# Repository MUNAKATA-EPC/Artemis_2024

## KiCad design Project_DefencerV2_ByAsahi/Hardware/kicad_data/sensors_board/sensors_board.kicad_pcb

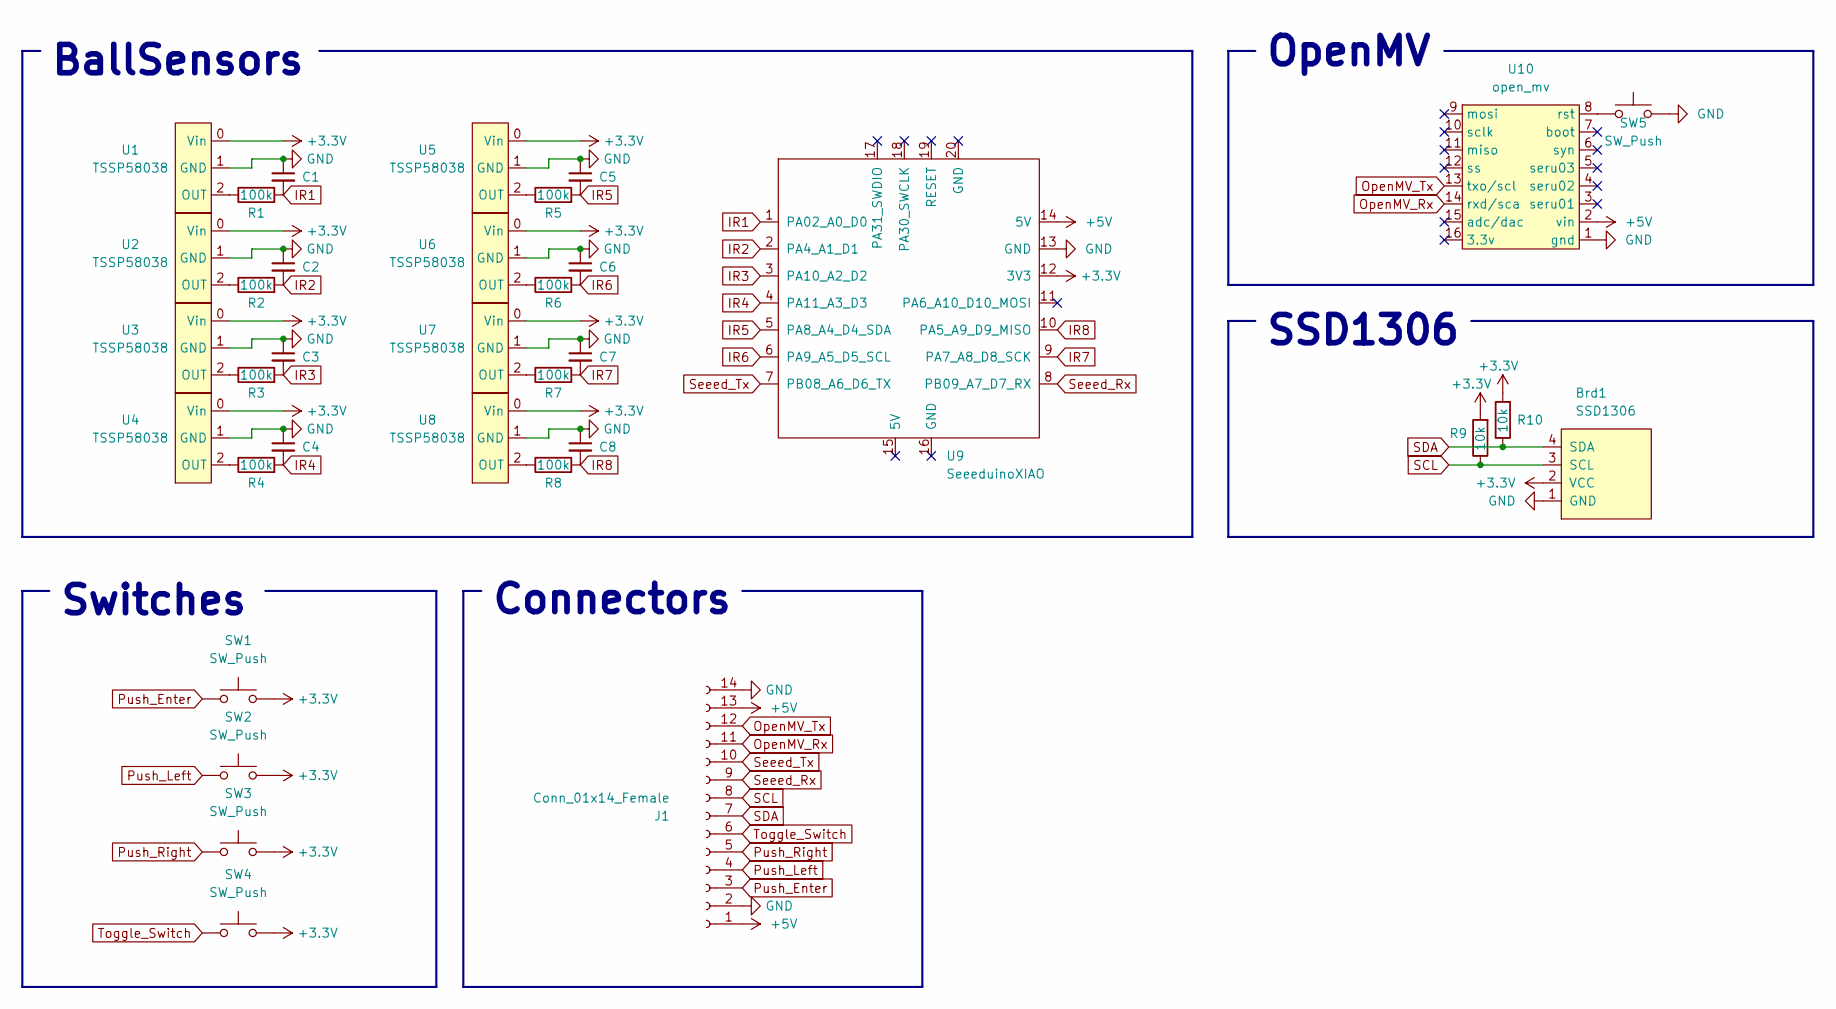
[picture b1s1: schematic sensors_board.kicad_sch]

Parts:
Brd1: SSD1306; 128x64OLED
C1, C2, C3, C4, C5, C6, C7, C8: C_Small; C_Disc_D3.0mm_W2.0mm_P2.50mm
J1: Conn_01x14_Female; IDC-Header_2x07_P2.54mm_Horizontal
R1, R2, R3, R4, R5, R6, R7, R8: 100k; R_Axial_DIN0204_L3.6mm_D1.6mm_P5.08mm_Horizontal
R9, R10: 10k; R_Axial_DIN0204_L3.6mm_D1.6mm_P5.08mm_Horizontal
SW1, SW2, SW3, SW5: SW_Push; SW_PUSH_6mm_H5mm
SW4: SW_Push; DS-850k
U1, U2, U3, U4, U5, U6, U7, U8: TSSP58038
U9: SeeeduinoXIAO; seeeduinoXIAO
U10: open_mv; OpenMV

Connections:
+3.3V: Brd1.2 (VCC), R9.2, R10.2, SW1.2, SW2.2, SW3.2, SW4.2, U1.0 (Vin), U2.0 (Vin), U3.0 (Vin), U4.0 (Vin), U5.0 (Vin), U6.0 (Vin), U7.0 (Vin), U8.0 (Vin), U9.12 (3V3)
+5V: J1.1, J1.13, U9.14 (5V), U10.2 (vin)
GND: Brd1.1 (GND), C1.1, C2.1, C3.1, C4.1, C5.1, C6.1, C7.1, C8.1, J1.2, J1.14, SW5.2, U1.1 (GND), U2.1 (GND), U3.1 (GND), U4.1 (GND), U5.1 (GND), U6.1 (GND), U7.1 (GND), U8.1 (GND), U9.13 (GND), U10.1 (gnd)
IR1: C1.2, R1.2, U9.1 (PA02_A0_D0)
IR2: C2.2, R2.2, U9.2 (PA4_A1_D1)
IR3: C3.2, R3.2, U9.3 (PA10_A2_D2)
IR4: C4.2, R4.2, U9.4 (PA11_A3_D3)
IR5: C5.2, R5.2, U9.5 (PA8_A4_D4_SDA)
IR6: C6.2, R6.2, U9.6 (PA9_A5_D5_SCL)
IR7: C7.2, R7.2, U9.9 (PA7_A8_D8_SCK)
IR8: C8.2, R8.2, U9.10 (PA5_A9_D9_MISO)
unnamed: R1.1, U1.2 (OUT)
unnamed: R2.1, U2.2 (OUT)
unnamed: R3.1, U3.2 (OUT)
unnamed: R4.1, U4.2 (OUT)
unnamed: R5.1, U5.2 (OUT)
unnamed: R6.1, U6.2 (OUT)
unnamed: R7.1, U7.2 (OUT)
unnamed: R8.1, U8.2 (OUT)
unnamed: SW5.1, U10.8 (rst)
OpenMV_Rx: J1.11, U10.14 (rxd/sca)
OpenMV_Tx: J1.12, U10.13 (txo/scl)
Push_Enter: J1.3, SW1.1
Push_Left: J1.4, SW2.1
Push_Right: J1.5, SW3.1
SCL: Brd1.3 (SCL), J1.8, R9.1
SDA: Brd1.4 (SDA), J1.7, R10.1
Seeed_Rx: J1.9, U9.8 (PB09_A7_D7_RX)
Seeed_Tx: J1.10, U9.7 (PB08_A6_D6_TX)
Toggle_Switch: J1.6, SW4.1

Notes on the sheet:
Connectors
SSD1306
BallSensors
Switches
OpenMV

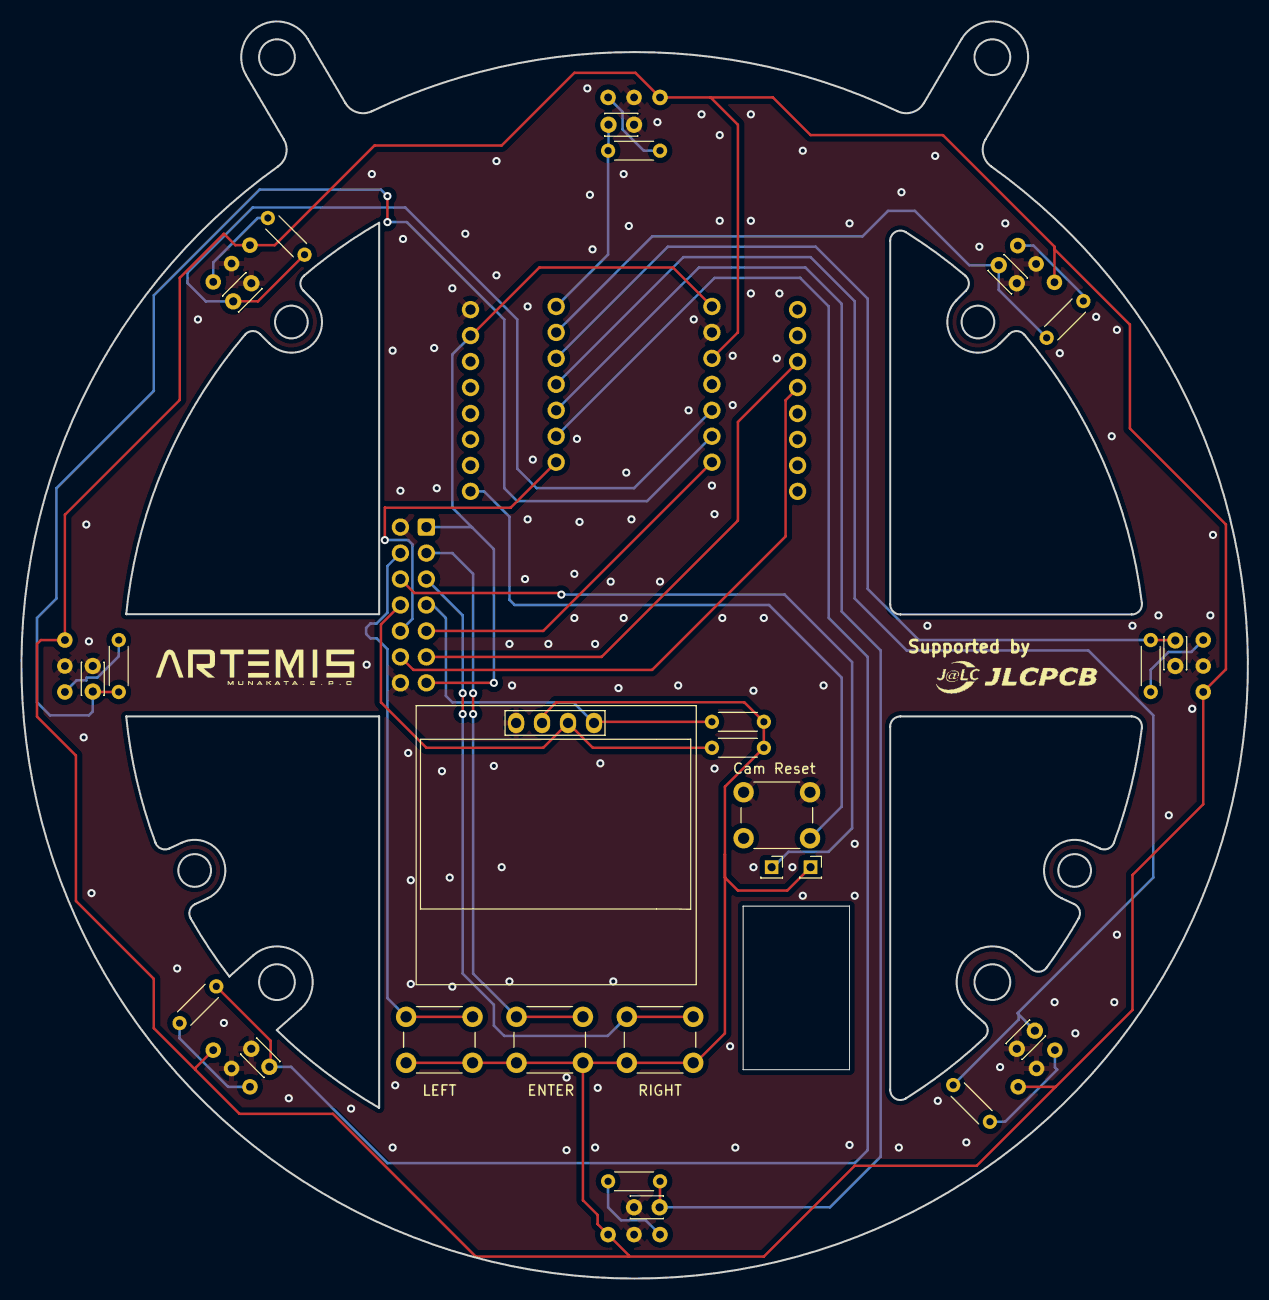
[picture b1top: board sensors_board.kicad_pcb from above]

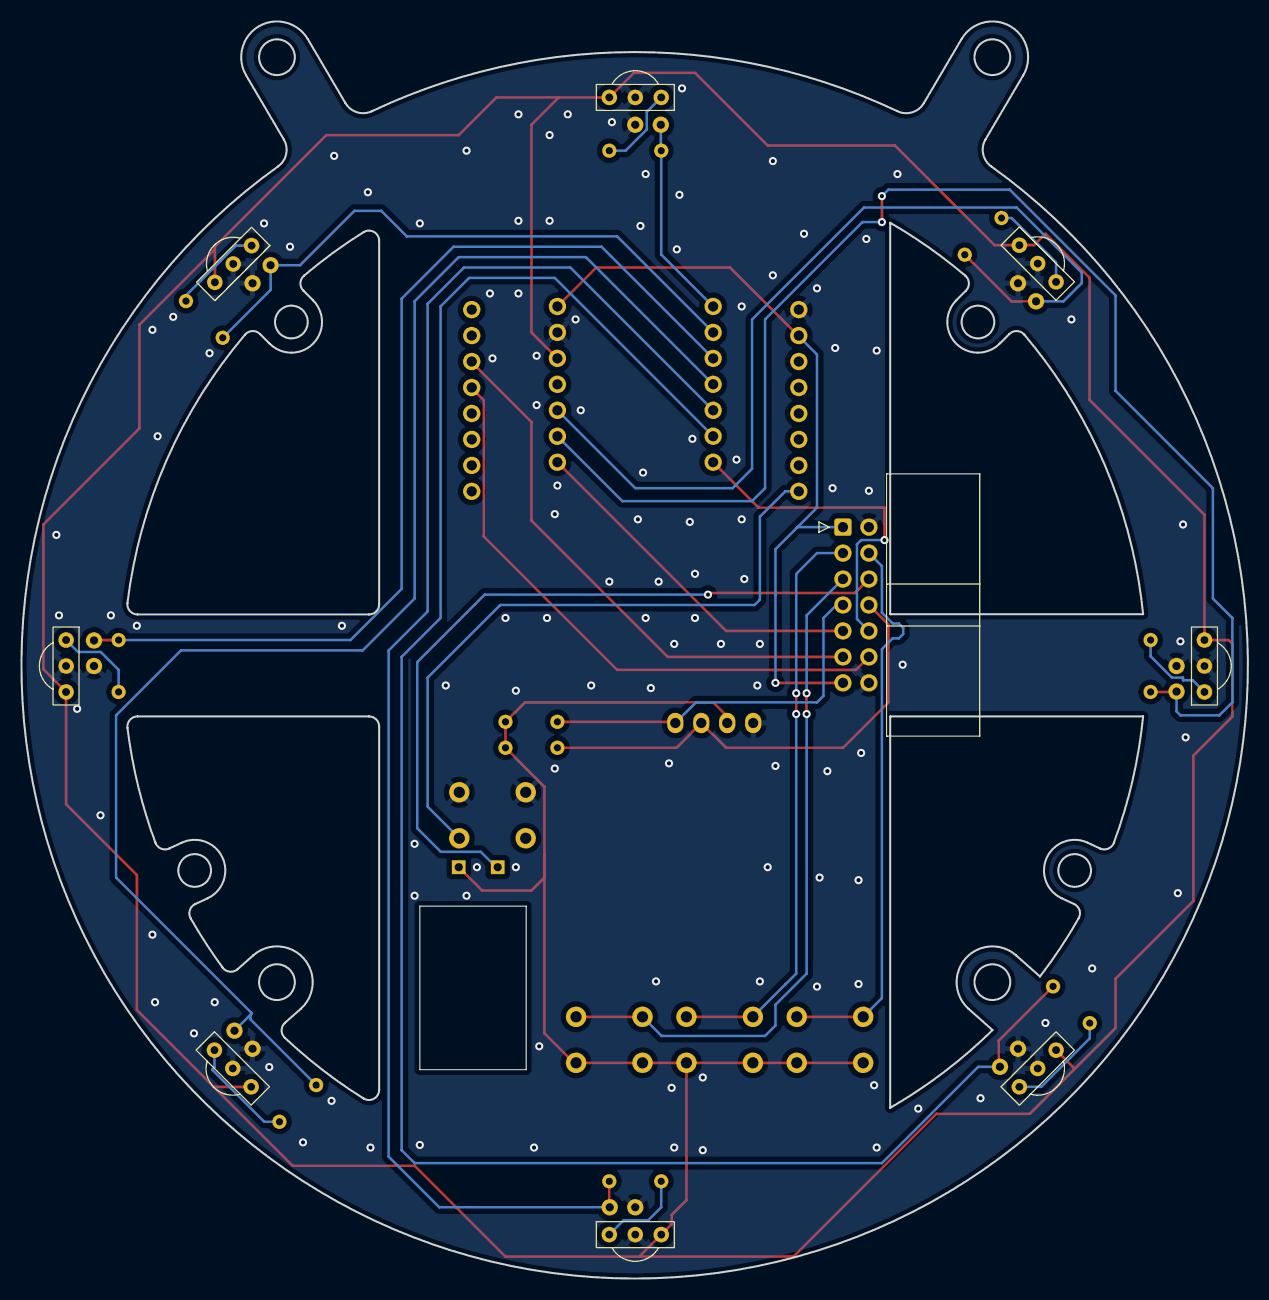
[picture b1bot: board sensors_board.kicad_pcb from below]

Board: 2 copper layers, 120.0 x 123.0 mm, 34 parts (10 on the bottom side), 29 nets.

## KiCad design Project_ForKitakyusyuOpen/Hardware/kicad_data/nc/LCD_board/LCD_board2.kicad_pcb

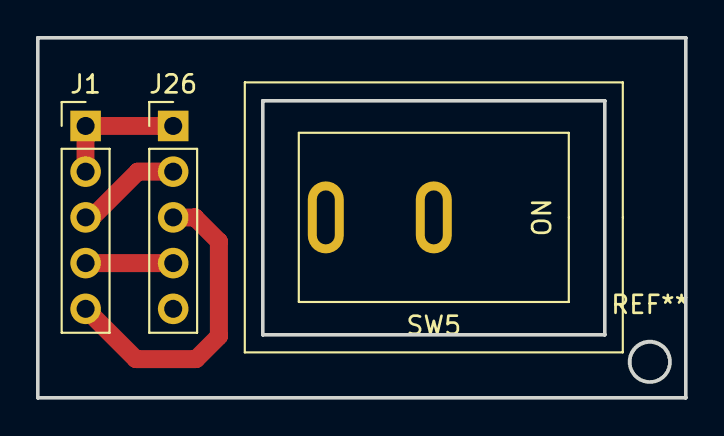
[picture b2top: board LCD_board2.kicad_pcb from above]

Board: 2 copper layers, 36.0 x 20.0 mm, 3 parts (0 on the bottom side), 5 nets.

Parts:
J1, J26: Conn_01x05_Socket; PinHeader_1x05_P2.54mm_Vertical
SW5: SW_DIP_x01; DS-850k

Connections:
+3V3: J1.1, J1.2, J26.1, SW5.1
D9: J26.5, SW5.2
GND: J1.5, J26.3
SCL0: J1.3, J26.2
SDA0: J1.4, J26.4

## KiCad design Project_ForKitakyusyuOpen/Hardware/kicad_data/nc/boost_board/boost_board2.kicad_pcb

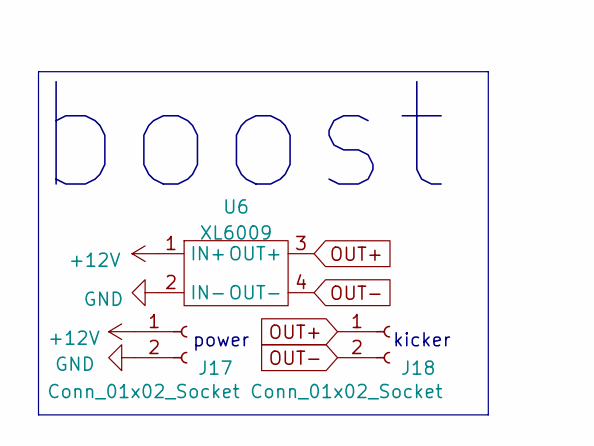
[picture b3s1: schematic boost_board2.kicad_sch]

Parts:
J17, J18: Conn_01x02_Socket; PinHeader_1x02_P2.54mm_Vertical
U6: XL6009

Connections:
+12V: J17.1, U6.1 (IN+)
GND: J17.2, U6.2 (IN-)
OUT+: J18.1, U6.3 (OUT+)
OUT-: J18.2, U6.4 (OUT-)

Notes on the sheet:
kicker
power
boost

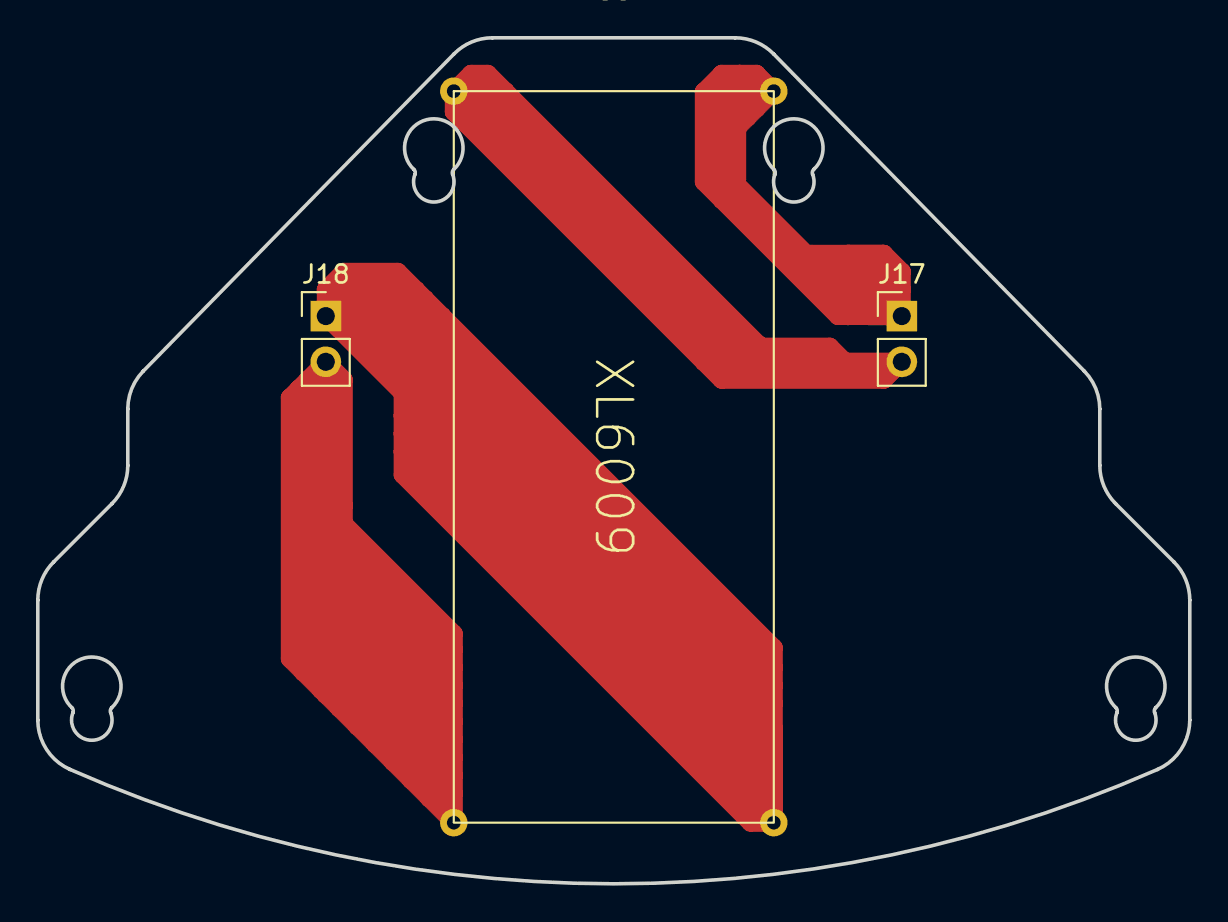
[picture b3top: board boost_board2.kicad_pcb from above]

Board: 2 copper layers, 64.0 x 47.0 mm, 3 parts (0 on the bottom side), 4 nets.

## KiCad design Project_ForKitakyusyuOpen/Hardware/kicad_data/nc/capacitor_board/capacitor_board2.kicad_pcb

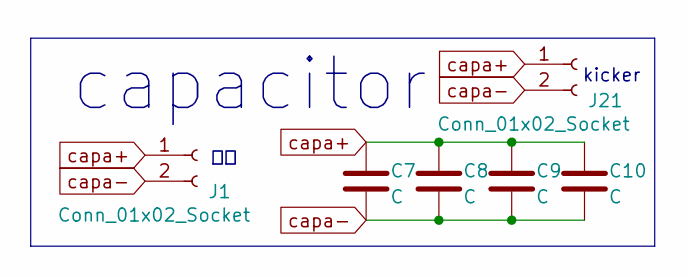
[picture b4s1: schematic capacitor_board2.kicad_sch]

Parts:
C7, C8, C9, C10: C; CP_Radial_D12.5mm_P5.00mm
J1, J21: Conn_01x02_Socket; PinHeader_1x02_P2.54mm_Vertical

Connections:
capa+: C7.1, C8.1, C9.1, C10.1, J1.1, J21.1
capa-: C7.2, C8.2, C9.2, C10.2, J1.2, J21.2

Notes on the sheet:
capacitor
kicker

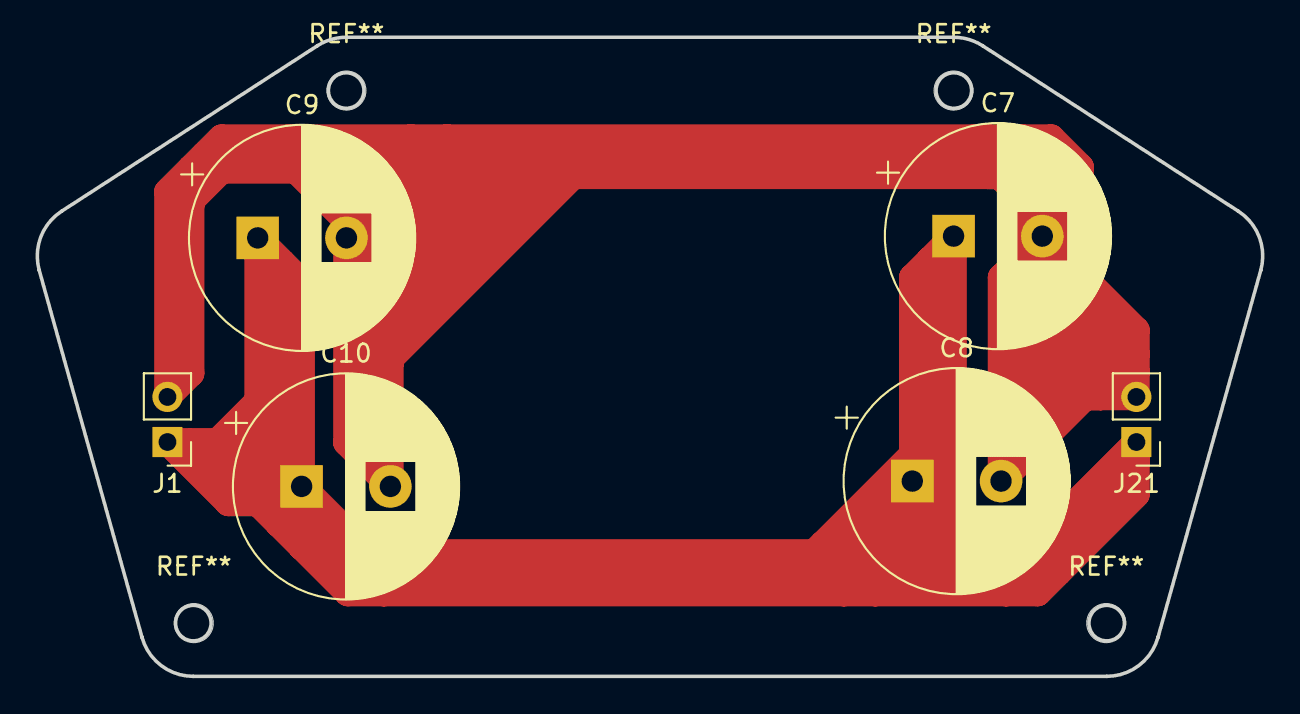
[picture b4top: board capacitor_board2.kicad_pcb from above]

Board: 2 copper layers, 69.0 x 36.0 mm, 6 parts (0 on the bottom side), 2 nets.

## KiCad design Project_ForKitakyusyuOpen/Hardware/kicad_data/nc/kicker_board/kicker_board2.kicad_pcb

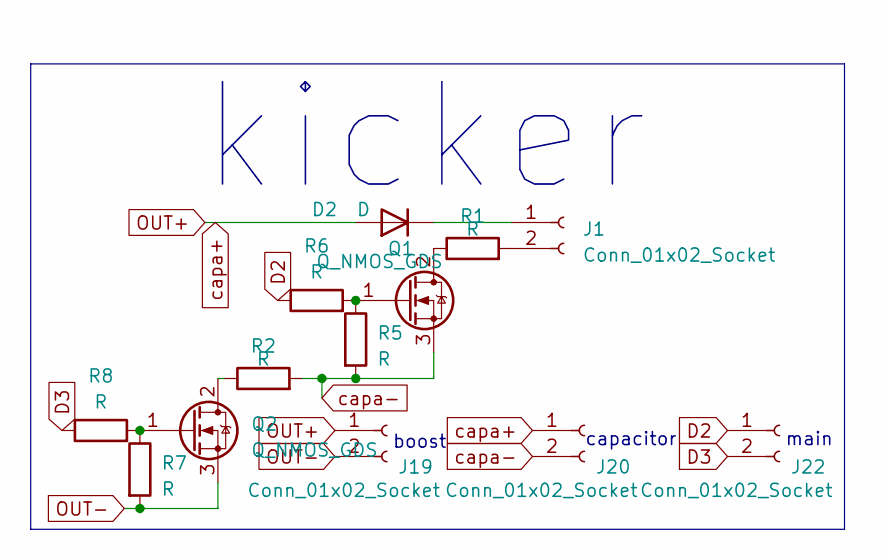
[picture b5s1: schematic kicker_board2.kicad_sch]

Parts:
D2: D; D_5W_P12.70mm_Horizontal
J1, J19, J20, J22: Conn_01x02_Socket; PinHeader_1x02_P2.54mm_Vertical
Q1: Q_NMOS_GDS; FET
Q2: Q_NMOS_GDS; PinHeader_1x03_P2.54mm_Vertical
R1, R2: R; 5W 1Ω sement
R5, R6, R7, R8: R; R_Axial_DIN0207_L6.3mm_D2.5mm_P7.62mm_Horizontal

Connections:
D2: J22.1, R6.1
D3: J22.2, R8.1
unnamed: D2.1 (K), J1.1
unnamed: J1.2, R1.2
unnamed: Q1.2 (D), R1.1
unnamed: Q1.1 (G), R5.1, R6.2
unnamed: Q2.2 (D), R2.1
unnamed: Q2.1 (G), R7.1, R8.2
OUT+: D2.2 (A), J19.1, J20.1
OUT-: J19.2, Q2.3 (S), R7.2
capa-: J20.2, Q1.3 (S), R2.2, R5.2

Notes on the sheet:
main
kicker
capacitor
boost

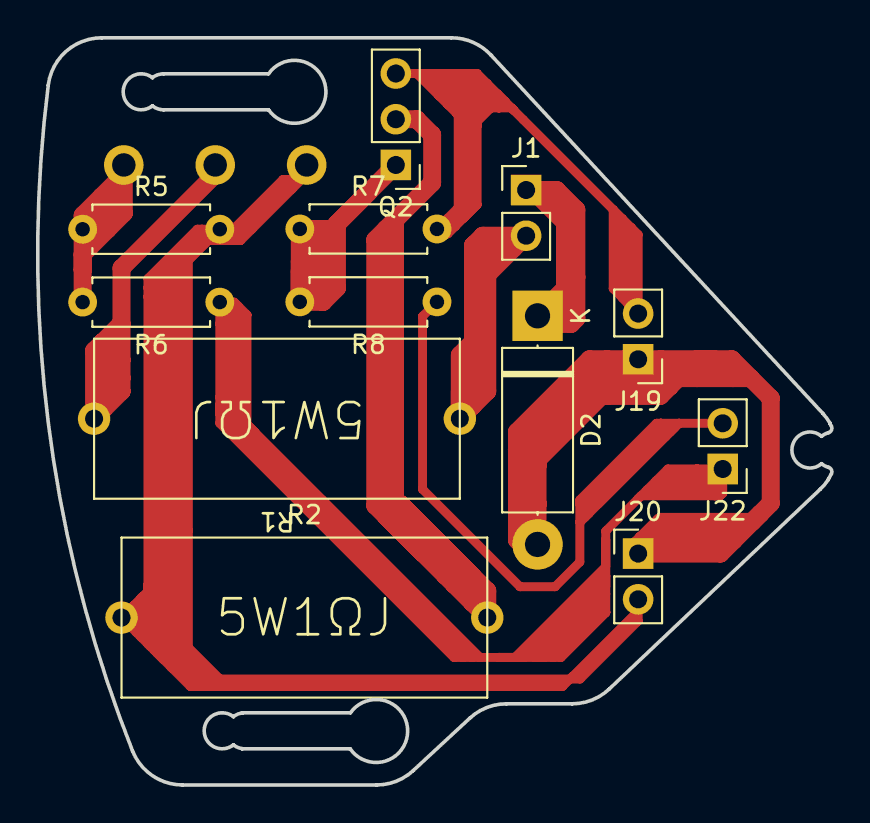
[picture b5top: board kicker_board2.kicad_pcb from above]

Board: 2 copper layers, 44.1 x 41.5 mm, 13 parts (0 on the bottom side), 11 nets.

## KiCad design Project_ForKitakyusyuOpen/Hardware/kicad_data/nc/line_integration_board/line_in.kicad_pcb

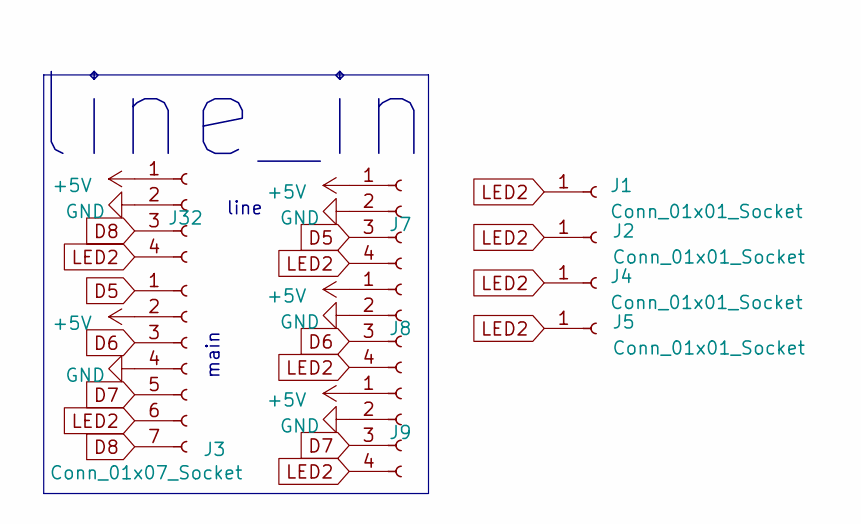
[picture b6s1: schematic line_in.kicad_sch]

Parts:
J1, J2, J4, J5: Conn_01x01_Socket; PinHeader_1x01_P2.54mm_Vertical
J3: Conn_01x07_Socket; PinHeader_1x07_P2.54mm_Vertical
J7, J8, J9, J32: Conn_01x04_Socket; PinSocket_1x04_P2.54mm_Horizontal

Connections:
+5V: J3.2, J7.1, J8.1, J9.1, J32.1
D5: J3.1, J7.3
D6: J3.3, J8.3
D7: J3.5, J9.3
D8: J3.7, J32.3
GND: J3.4, J7.2, J8.2, J9.2, J32.2
LED2: J1.1, J2.1, J3.6, J4.1, J5.1, J7.4, J8.4, J9.4, J32.4

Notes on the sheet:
main
line
line_in

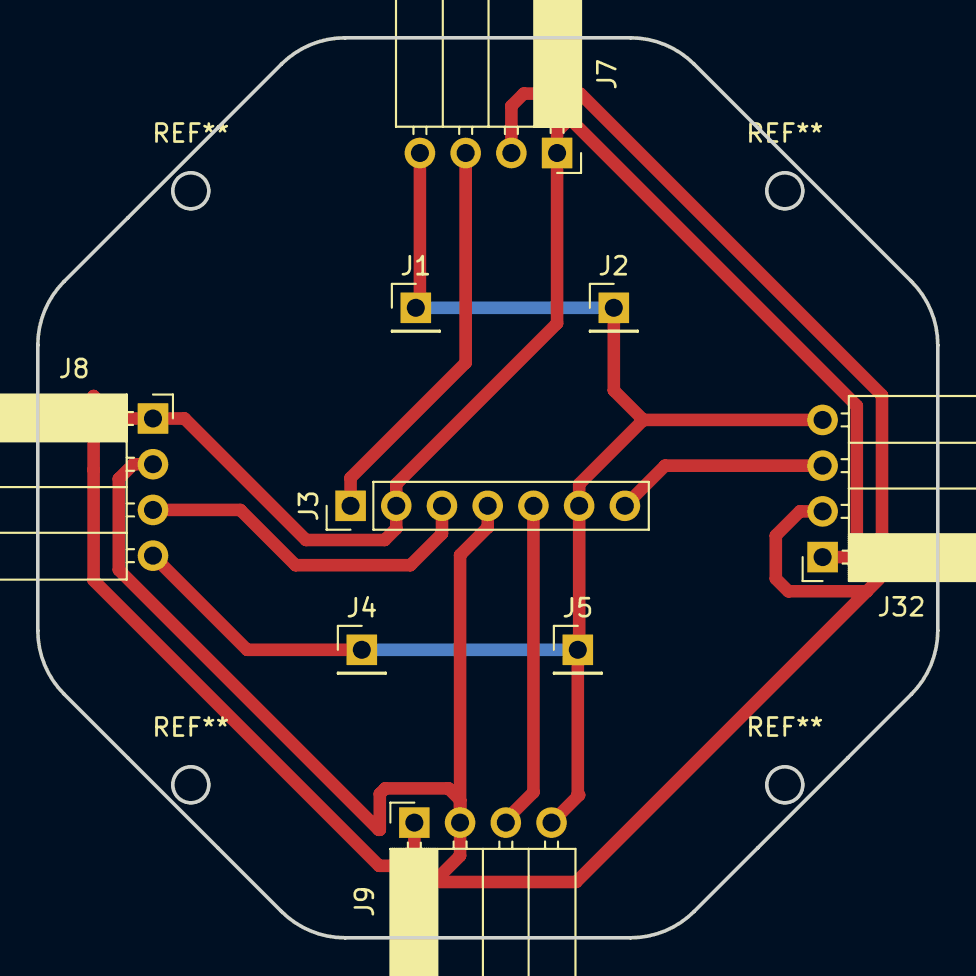
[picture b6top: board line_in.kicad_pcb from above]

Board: 2 copper layers, 50.0 x 50.0 mm, 9 parts (0 on the bottom side), 7 nets.

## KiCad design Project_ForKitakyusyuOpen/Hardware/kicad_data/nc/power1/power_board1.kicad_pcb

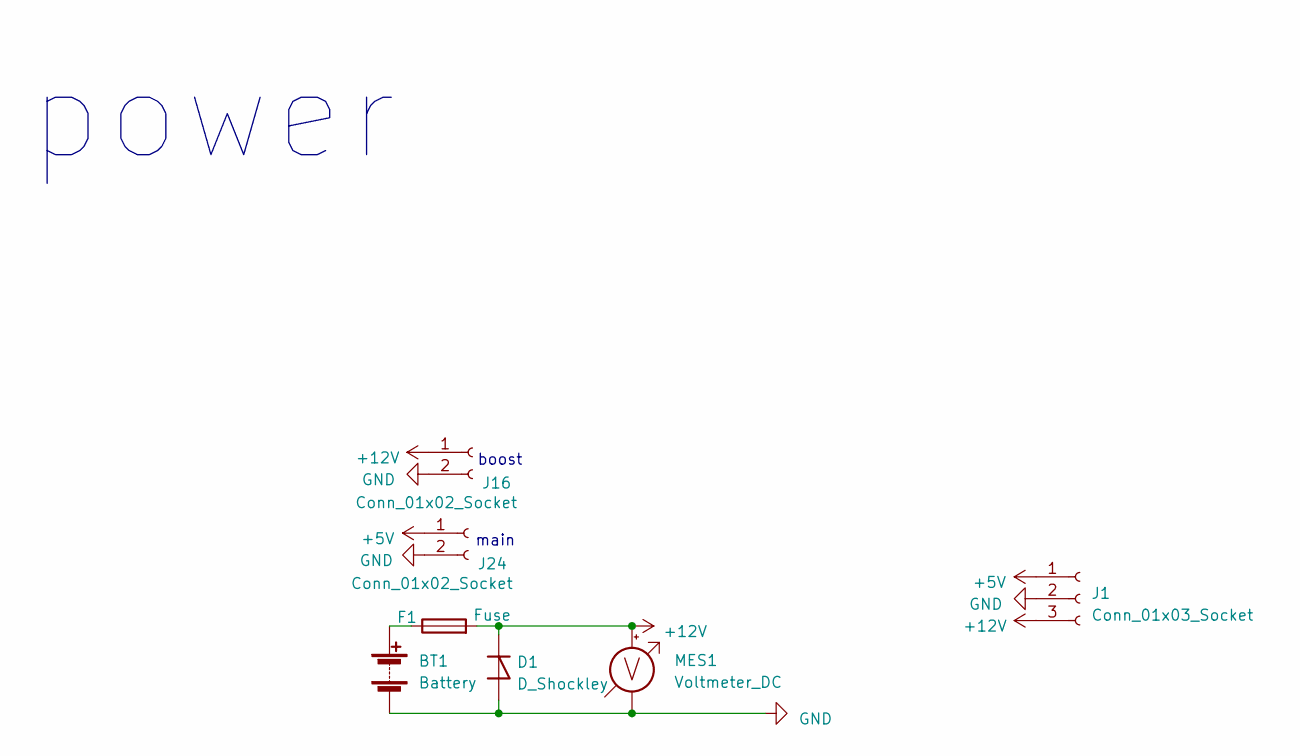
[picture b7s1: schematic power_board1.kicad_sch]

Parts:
BT1: Battery; JST_VH_B2P-VH-B_1x02_P3.96mm_Vertical
D1: D_Shockley; D_5W_P12.70mm_Horizontal
F1: Fuse; fuse_socket
J1: Conn_01x03_Socket; PinHeader_1x03_P2.54mm_Vertical
J16, J24: Conn_01x02_Socket; PinHeader_1x02_P2.54mm_Vertical
MES1: Voltmeter_DC; PinHeader_1x02_P2.54mm_Vertical

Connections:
+5V: J1.1, J24.1
+12V: D1.1 (K), F1.2, J1.3, J16.1, MES1.2 (+)
GND: BT1.2 (-), D1.2 (A), J1.2, J16.2, J24.2, MES1.1 (-)
unnamed: BT1.1 (+), F1.1

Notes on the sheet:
main
power
boost

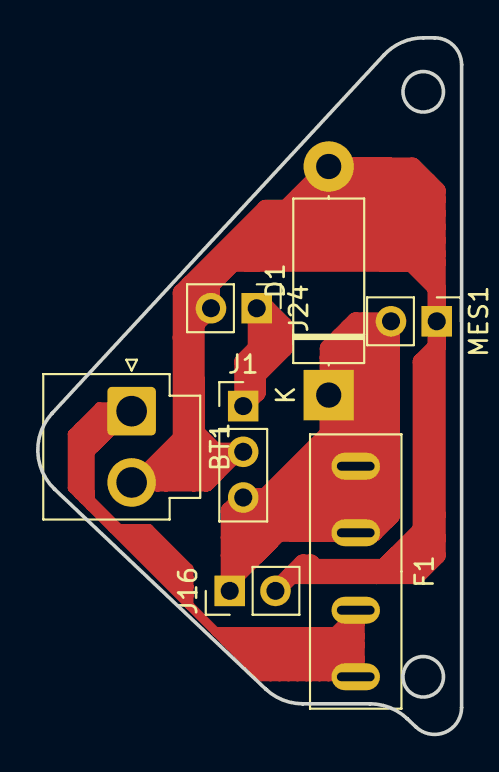
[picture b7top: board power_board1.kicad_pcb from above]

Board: 2 copper layers, 23.5 x 38.7 mm, 7 parts (0 on the bottom side), 4 nets.

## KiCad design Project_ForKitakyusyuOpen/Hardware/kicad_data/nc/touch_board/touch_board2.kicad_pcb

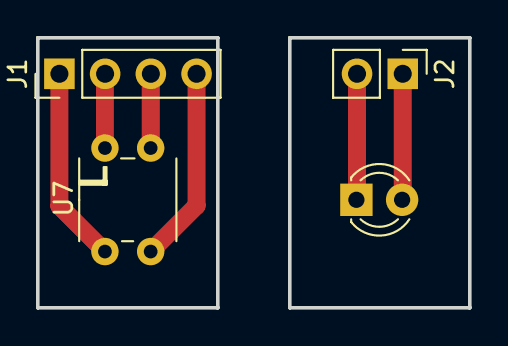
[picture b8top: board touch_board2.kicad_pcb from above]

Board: 2 copper layers, 24.0 x 15.0 mm, 4 parts (0 on the bottom side), 5 nets.

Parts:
D3: LED; LED_D3.0mm_Clear
J1: Conn_01x04_Socket; PinHeader_1x04_P2.54mm_Vertical
J2: Conn_01x02_Socket; PinHeader_1x02_P2.54mm_Vertical
U7: Line_sennsor; S4282-51

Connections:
+5V: J1.4, U7.2 (VCC)
D4: J1.3, U7.3 (VOUT)
GND: J1.2, U7.4 (GND)
K1(-): D3.1 (K), J1.1, J2.2, U7.1 (K(-))
LED1: D3.2 (A), J2.1
